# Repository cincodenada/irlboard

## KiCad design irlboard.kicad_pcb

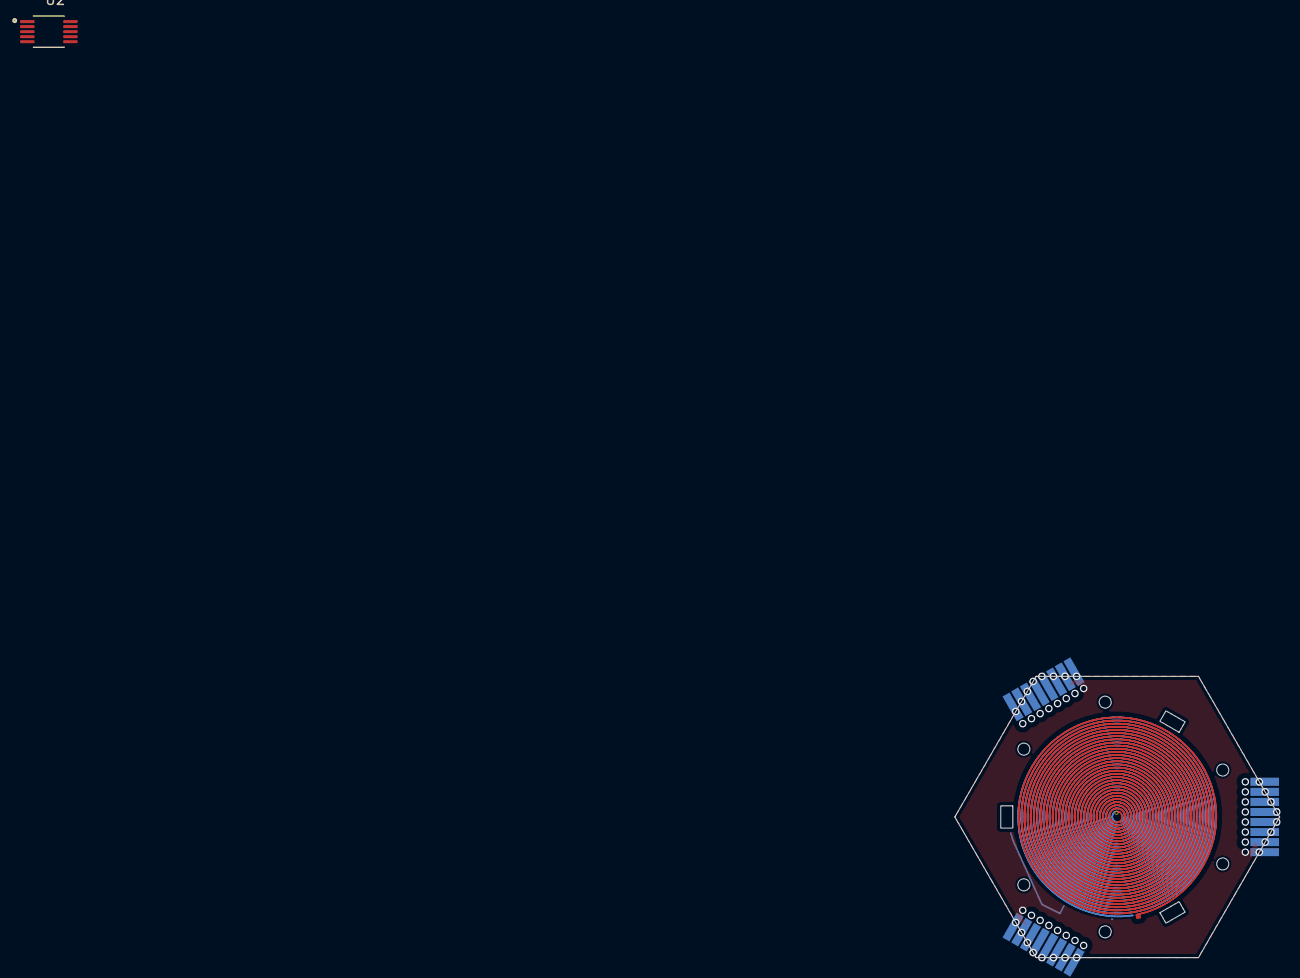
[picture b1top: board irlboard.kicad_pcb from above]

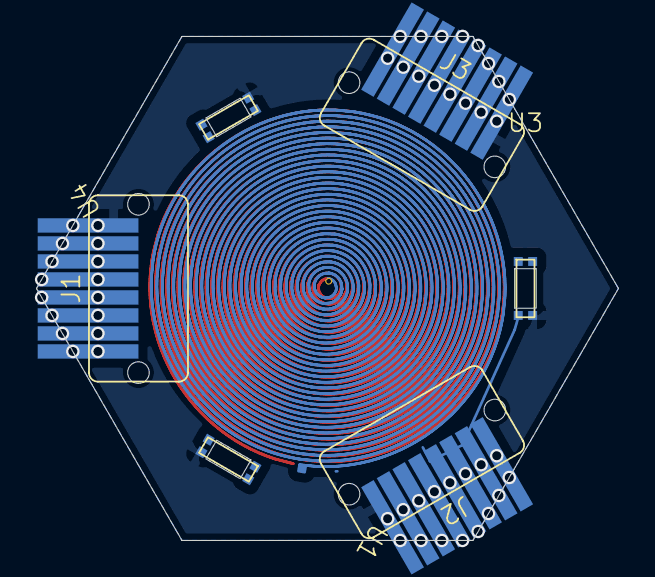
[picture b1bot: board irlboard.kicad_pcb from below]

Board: 2 copper layers, 32.3 x 28.0 mm, 8 parts (6 on the bottom side), 12 nets.

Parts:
J1, J2, J3: Stacker-8pos-mate
L1: ElectromagneticActor; Coil_2Side_20mm
U1, U3, U4: B3DQ3BRG-05C000113U1930_Flip
U2: 74LVC2G3157DPJ; SOP50P490X110-10N

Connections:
GND: J1.8, J2.8, J3.8, U1.1 (VSS), U3.1 (VSS), U4.1 (VSS)
unnamed: J1.4, U3.3 (DIN)
unnamed: J1.5, U3.4 (DOUT)
unnamed: J1.6, J2.6, J3.6, L1.2 (+)
unnamed: J1.7, J2.7, J3.7, L1.1 (-)
unnamed: J2.4, U1.3 (DIN)
unnamed: J2.5, U1.4 (DOUT)
unnamed: J3.4, U4.3 (DIN)
unnamed: J3.5, U4.4 (DOUT)
unnamed: U2.2 (1Y1), U2.3 (GND), U2.4 (2Y1)
VCC: J1.1, J2.1, J3.1, U1.2 (VDD), U2.8 (VCC), U3.2 (VDD), U4.2 (VDD)
Vdrive: U2.7 (2Y0), U2.9 (1Y0)

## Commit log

2024-12-06 Initial commit I guess
